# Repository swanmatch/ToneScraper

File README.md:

# ToneScraper

## 概要

[せきごんさん](https://github.com/sekigon-gonnoc)の[mtch6102評価基板](https://github.com/sekigon-gonnoc/mtch6102_breakout)を参考に、タッチパッドとロータリーエンコーダーを3機搭載した4キーマイクロパッド。

ロータリーエンコーダーは単色の光るエンコーダーかプッシュスイッチ付きのもののどちらか選んで実装できます。

## 部品リスト

| 品目                         | 数量 | 備考 |
| :--------------------------- | ---: | :--- |
| PCB                          |  1枚 |  |
| トッププレート               |  1枚 |  |
| ボトムプレート               |  1枚 |  |
| ProMicro                     |  1個 |  |
| コンスルー                   |  2本 |  |
| LED(SK6812mini)              |  4個 |  |
| MTCH6102                     |  1個 |  |
| レベル変換基板               |  1個 | https://nogikes.booth.pm/items/2008258 |
| 4pinピンヘッダー             |  1個 |  |
| ハーフピッチ5pinピンヘッダー |  1個 |  |
| アナログ5mm砲丸LED           |  1個 |  |
| 220Ω抵抗                    |  1個 |  |
| M2L8丸スペーサ               |  4本 |  |
| M2L7六角スペーサ(オスメス)   |  6本 |  |
| M2L4ネジ                     |  8本 |  |
| アングルタクトスイッチ       |  1個 |  |
| ゴム足                       |  4個 |  |
| KailhChocスイッチ            |  4個 |  |
| 1Uキーキャップ               |  4個 |  |
| USBケーブル                  |  1本 |  |
| TRRS JACK                    |  2個 | パームレスト for SilverbulletRequiemを光らせる場合 |
| TRRSまたはTRSケーブル        |  2本 | パームレスト for SilverbulletRequiemを光らせる場合必|
| 圧電サウンダ(PKLCS1212)      |  1個 | 圧電サウンダを実装する場合 |
| ダイオード                   |  1個 | 圧電サウンダを実装する場合 |
| 1KΩ抵抗                     |    1個 | 圧電サウンダを実装する場合 |
| 光るロータリーエンコーダー   | 3個 | [赤](https://akizukidenshi.com/catalog/g/gP-05762/) [青](https://akizukidenshi.com/catalog/g/gP-05768/) [黄緑](https://akizukidenshi.com/catalog/g/gP-05767/) |
| 100Ω抵抗                    |  3個 | 光るロータリーエンコーダーを実装する場合 |
| 通常ロータリーエンコーダー  |  3個 |  |

## 組み立て手順

### LEDの実装

LEDをはんだ付けします。  
欠けている足が右上の三角のシルクに対応します。

### アナログLED・抵抗の実装

アナログLEDの横の抵抗とLEDを実はんだ付けします。

LEDは数ミリ浮かせた状態で実装して、トッププレートを付けたときにはみ出るとかっこいいです。

圧電サウンダを使う場合、ダイオードと1kΩ抵抗、圧電サウンダを、
光るエンコーダーを使う場合、その他の抵抗のフットプリントに100Ω抵抗を実装します。

＊) 圧電サウンダの実装を忘れて写真を撮りました…！

### リセットスイッチ、TRRSジャックの実装

TRRSジャックと、タクトスイッチを実装します。

### レベル変換基板用のピンヘッダの実装

レベル変換基板用のピンヘッダをはんだ付けします。

標準ピッチ基板は表(スイッチ面)から見て一番右側は使っていないので左寄せにします。

ピンヘッダを傾けてはんだ付けしてしまうと変換基板がハマらないので、
変換基板を載せた状態でマスキングテープで固定して、裏からはんだ付けします。

続いてレベル変換基板をはんだ付けします。

### Chocスイッチとロータリーエンコーダーの実装

ロータリーエンコーダーとChocスイッチをはんだ付けします。

＊) chocの実装を忘れて写真を撮りました…！

### MTCH6102の実装

MTCH6102をトッププレートに実装します。  
ICに付いている丸い印が右上です。

### スペーサーの実装

スペーサーをはめます。  
上に丸、下に六角です。

### ネジ止め

トッププレート、ボトムプレートを挟んでネジ止めします。
ボトムプレートはリバーシブルで使えます。

### キャップ

ロータリーエンコーダー、Chocスイッチのキャップをはめて完成です！

## ファームウェア

ファームウェアは(ここ)[https://github.com/swanmatch/qmk_firmware/tree/master/keyboards/tone_scraper]に置いてあります。

以下の手順で書き込みます。

QMKの環境構築についてはお使いのOSによって異なりなりますので、
(公式ドキュメント)を読んでください。

```sh
git clone https://github.com/swanmatch/qmk_firmware.git
cd qmk_firmware
make git-submodule
make tone_scraper:default:avrdude
```

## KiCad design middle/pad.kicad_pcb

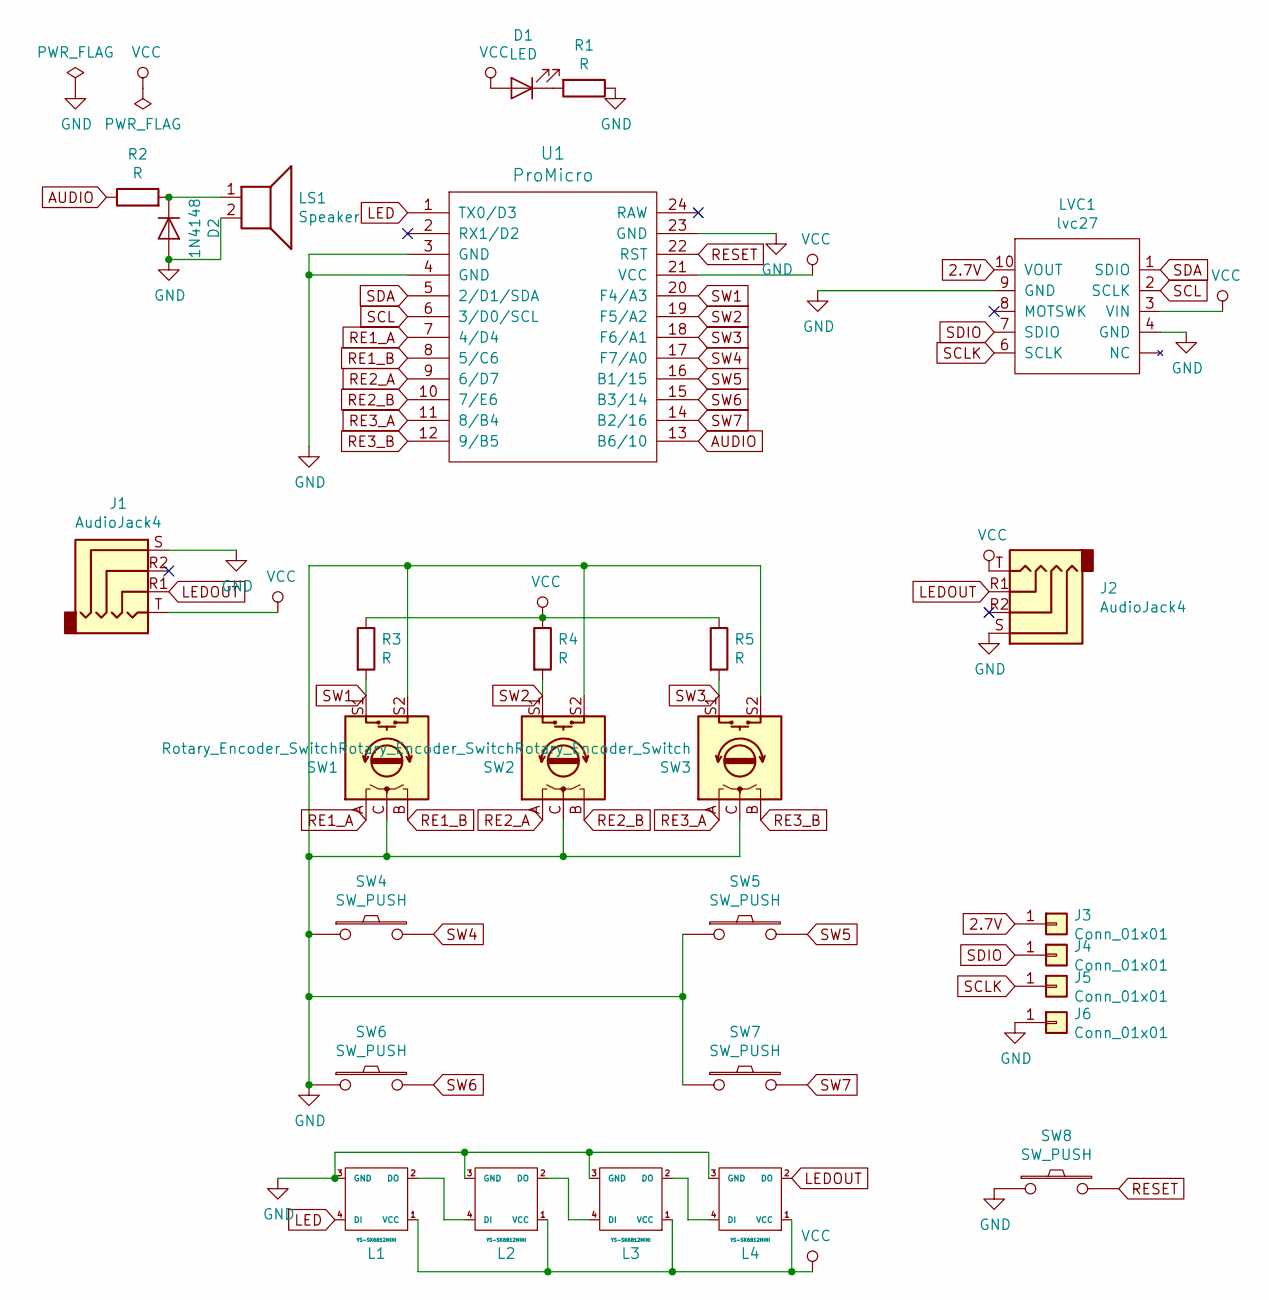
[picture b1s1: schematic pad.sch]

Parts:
D1: LED; LED_D5.0mm
D2: 1N4148; D3_TH_SMD
J1, J2: AudioJack4; MJ-4PP-9_1side
J3, J4, J5, J6: Conn_01x01; MountingHole_2.2mm_M2_Pad_Via
L1, L2, L3, L4: YS-SK6812MINI; YS-SK6812MINI-E
LS1: Speaker; PKLCS1212E4001
LVC1: lvc27
R1, R2, R3, R4, R5: R; Resistor-Hybrid
SW1, SW2, SW3: Rotary_Encoder_Switch; RotaryEncoder_Alps_EC12E-Switch_Vertical_H20mm
SW4, SW5, SW6, SW7: SW_PUSH; Choc_1u
SW8: SW_PUSH; SW_Tactile_SPST_Angled_PTS645Vx39-2LFS
U1: ProMicro; ProMicro_v3

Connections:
2.7V: J3.1, LVC1.10 (VOUT)
AUDIO: R2.1, U1.13 (B6/10)
GND: D2.2 (A), J1.S, J2.S, J6.1, L1.3 (GND), L2.3 (GND), L3.3 (GND), L4.3 (GND), LS1.2, LVC1.4 (GND), LVC1.9 (GND), R1.1, SW1.C, SW1.MP, SW1.S2, SW2.C, SW2.MP, SW2.S2, SW3.C, SW3.MP, SW3.S2, SW4.1, SW5.1, SW6.1, SW7.1, SW8.1, U1.3 (GND), U1.4 (GND), U1.23 (GND)
LED: L1.4 (DI), U1.1 (TX0/D3)
LEDOUT: J1.R1, J2.R1, L4.2 (DO)
unnamed: D1.1 (K), R1.2
unnamed: D2.1 (K), LS1.1, R2.2
unnamed: L1.2 (DO), L2.4 (DI)
unnamed: L2.2 (DO), L3.4 (DI)
unnamed: L3.2 (DO), L4.4 (DI)
RE1_A: SW1.A, U1.7 (4/D4)
RE1_B: SW1.B, U1.8 (5/C6)
RE2_A: SW2.A, U1.9 (6/D7)
RE2_B: SW2.B, U1.10 (7/E6)
RE3_A: SW3.A, U1.11 (8/B4)
RE3_B: SW3.B, U1.12 (9/B5)
RESET: SW8.2, U1.22 (RST)
SCL: LVC1.2 (SCLK), U1.6 (3/D0/SCL)
SCLK: J5.1, LVC1.6 (SCLK)
SDA: LVC1.1 (SDIO), U1.5 (2/D1/SDA)
SDIO: J4.1, LVC1.7 (SDIO)
SW1: R3.2, SW1.S1, U1.20 (F4/A3)
SW2: R4.2, SW2.S1, U1.19 (F5/A2)
SW3: R5.2, SW3.S1, U1.18 (F6/A1)
SW4: SW4.2, U1.17 (F7/A0)
SW5: SW5.2, U1.16 (B1/15)
SW6: SW6.2, U1.15 (B3/14)
SW7: SW7.2, U1.14 (B2/16)
VCC: D1.2 (A), J1.T, J2.T, L1.1 (VCC), L2.1 (VCC), L3.1 (VCC), L4.1 (VCC), LVC1.3 (VIN), R3.1, R4.1, R5.1, U1.21 (VCC)

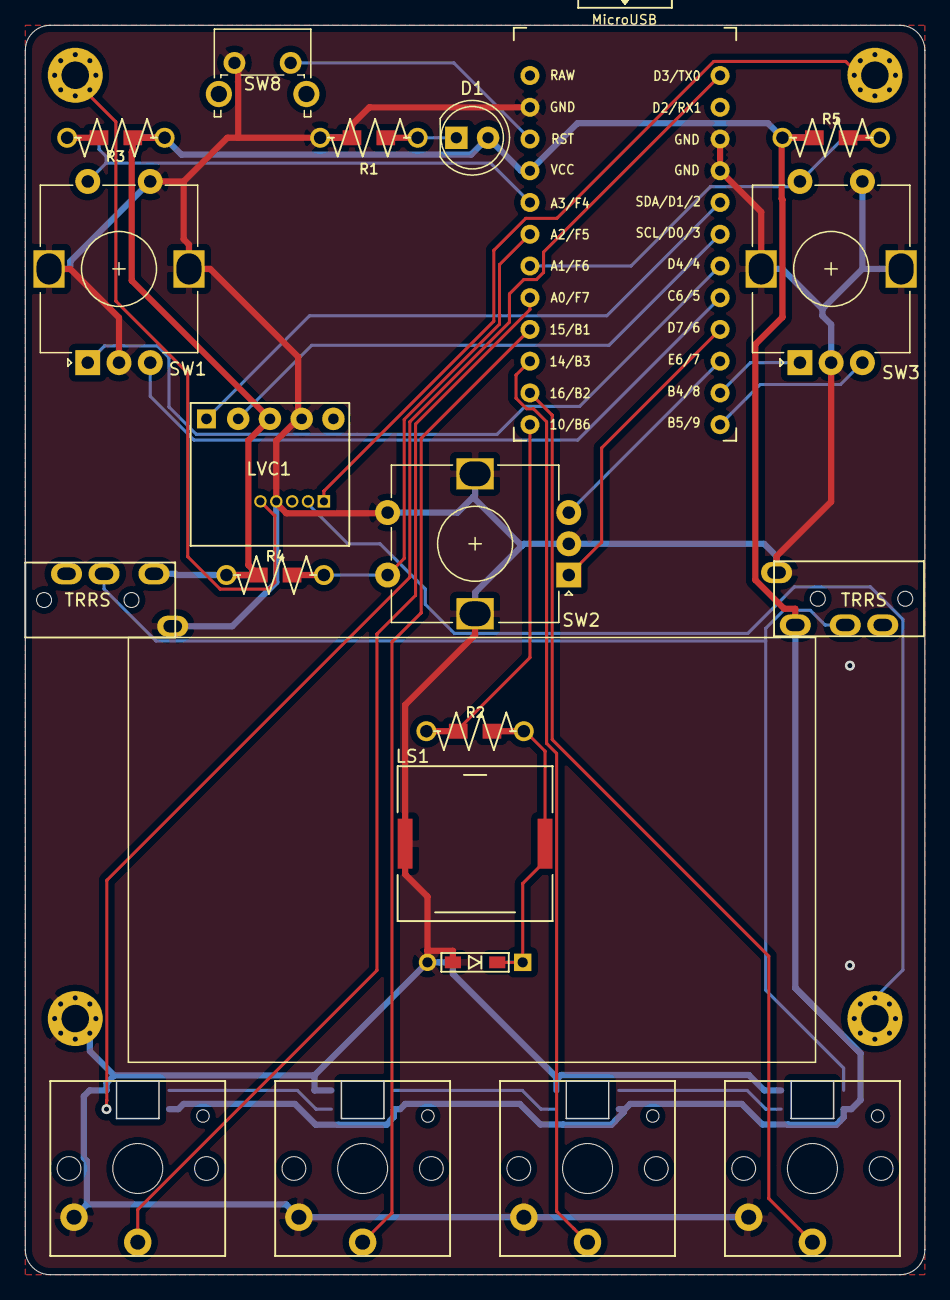
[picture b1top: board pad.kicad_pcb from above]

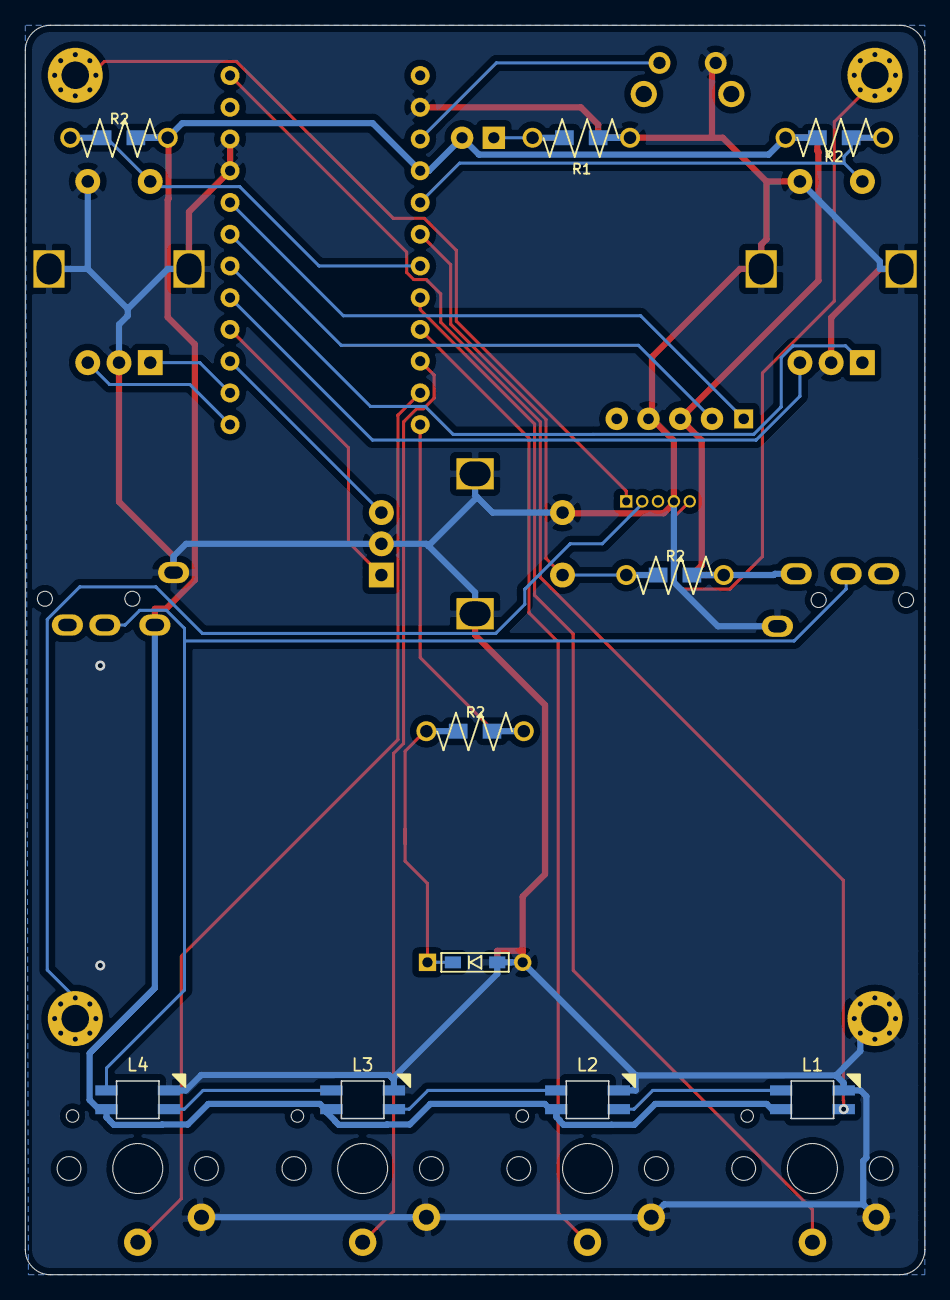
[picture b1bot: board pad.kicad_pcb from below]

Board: 2 copper layers, 71.9 x 99.9 mm, 28 parts (4 on the bottom side), 29 nets.

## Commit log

2021-05-15 clean
2021-05-15 Set theme jekyll-theme-dinky
2021-05-15 Set theme jekyll-theme-hacker
